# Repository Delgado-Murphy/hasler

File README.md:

# Hasler Music Box

<sub><i>A Delgado &amp; Murphy restoration</i></sub>

A Swiss radio from the 1960s that plays music again.

**Have a Hasler at home? → [Using your Hasler](docs/using.md)**

The **Hasler HM** was built in Bern around 1964 for Telefónica's *Hilo Musical*,
a service that sent music to homes over the telephone line. Its piano keys chose
one of six music channels. Today the same keys play internet radio, Spotify and
YouTube Music, and the radio is a speaker for your phone. The keys, the knobs,
the pilot lamp and the original speaker all still work.

## What it can do

- **Press a key, hear music.** No phone, no app.
- **Nearly 600 radio stations** from about 120 countries, each one played on
  a Hasler before it went in.
- **A speaker for your phone:** Spotify, AirPlay, Bluetooth and other music
  apps. Guests on your Wi-Fi can play too.
- **Several rooms.** Two or more Haslers play the same music in step.
- **Two knobs, like the old radio.** Volume, with a ceiling that protects the
  old speaker, and tone, which also switches the radio off.
- **A pilot lamp that talks:** amber for the radio, blue for a phone, a dim
  ember when asleep, dark when it is safe to unplug.
- **A key page** in your browser to choose the music on each key.
- **Safe updates** that install by themselves at night, and step back if
  something doesn't work.
- **Home Assistant**, if you want it. Everything works without it.

**Living with a Hasler?** [Using your Hasler](docs/using.md) starts with the
first ten minutes. The [pilot lamp](docs/lamp.md) has every colour, and
[Remote help](docs/remote-help.md) explains how the makers can look at your
radio from afar, only when you say so.

What changed in each version: the
[releases page](https://delgado-murphy.github.io/hasler-releases/).

---

## For makers and contributors

<!-- docs/img/hasler.jpg is a render of the HAT board for now; swap in a photo of the finished cabinet when there is one. -->

Inside: a Raspberry Pi, a modern amplifier and our own board (the Hasler
HAT), wired to the cabinet's original keys, knobs, lamp and speaker.

| You are... | Read this |
|---|---|
| **Building one** | [Build guide](docs/build-guide.md), then [Hardware](docs/hardware.md) |
| **Helping with the code** | [How it works](docs/architecture.md), then [Contributing](docs/contributing.md) |
| **Curious what changed** | [Releases](https://delgado-murphy.github.io/hasler-releases/) and the [changelog](CHANGELOG.md) |

**For makers**

- [Build guide](docs/build-guide.md): from an empty cabinet to a working radio, step by step.
- [A new SD card](docs/new-install.md): the radio's software from a blank card, headless, from a signed release.
- [Hardware](docs/hardware.md): parts list, wiring, power and protection.
- [The knobs' sound effects](docs/sound.md): the tone knob's effects and how a cabinet's knobs get them.
- [Multiroom and casting](docs/multiroom.md): how Haslers play in step (Snapcast), room names, AirPlay, UPnP, Bluetooth, Spotify.
- [The pilot lamp](docs/lamp.md): the light language, and the design the code follows.
- [Remote help](docs/remote-help.md): the makers' side, the tailnet and approving a radio.
- [Hasler HM panel survey](docs/variants/hasler-hm.md): measuring this cabinet's keys, knobs and speaker.
- [Prototype board](docs/prototype/README.md), and the Hasler HAT: [brief](docs/hat/BRIEF.md), [design](docs/hat/DESIGN.md), [ordering and bring-up](hardware/hat/ORDERING.md).

**For contributors and maintainers**

- [How the radio works](docs/architecture.md): the moving parts on one page, with diagrams.
- [Contributing](docs/contributing.md): where things are, running it on a laptop, the tests, how a cabinet's panel is described.
- [Security](SECURITY.md): how to report a security problem (privately, not in an issue).
- [Over-the-air updates](docs/ota.md): how updates stay safe.
- [Releasing](docs/release.md): how a new version is built, signed and published.
- [OTA formats](docs/ota-format.md): the exact file formats (a contract between the builder and the radio).

### How it works, in one picture

```
keys ───▶ MCP23017 (or Pi GPIO) ──┐
knobs ──▶ ADS1115 ────────────────┤
                                  ▼
                               haslerd ──▶ pilot lamp
                    ┌─────────────┼──────────────┬───────────────────┐
                    ▼             ▼              ▼                   ▼
             MPD (moOde)    go-librespot     key page :80/:8080   Home Assistant
          radio, YouTube      Spotify                            (optional)
              Music

MPD │ go-librespot │ Bluetooth │ AirPlay │ UPnP ──▶ Amp4 Pro (hardware mixer = the knob) ──▶ original speaker
                         │
                         └─ in a group: Snapcast ──▶ the other Haslers (each through its own amp and knob)
```

More detail, with diagrams: [How the radio works](docs/architecture.md).

`haslerd` is our small service on the Pi. It reads the keys and knobs, starts
the music, drives the lamp and serves the key page. The music system underneath
is [moOde audio](https://moodeaudio.org/). Bluetooth, AirPlay (shairport-sync)
and UPnP come from moOde; Spotify comes from go-librespot; YouTube Music
streams are found by yt-dlp; the tone knob's effects run in CamillaDSP
([sound.md](docs/sound.md)). Several Haslers play in step through
[Snapcast](https://github.com/badaix/snapcast) ([multiroom.md](docs/multiroom.md)).

**More cabinets are coming.** An *Excelsior* and others are waiting, and their
panels work differently (for example, keys that lock down). So the panel is
**data, not code**: one service, a few control types, and one YAML file per
cabinet in `config/variants/`.

### Licence

Hasler's code is [MIT](LICENSE). Two exceptions: the moOde patch in
`config/moode/` is GPL-3.0-or-later, because it changes moOde
([config/moode/LICENSE](config/moode/LICENSE)), and the HAT hardware design
(`hardware/hat/` and its notes in `docs/hat/`) is
[CERN-OHL-P-2.0](hardware/hat/LICENSE). Releases also bundle
go-librespot (GPL-3.0), Deno (MIT), two fonts (SIL OFL 1.1) and Python
packages under their own licences; [THIRD_PARTY_NOTICES.md](THIRD_PARTY_NOTICES.md)
lists them, and every release carries it with the full texts in `licenses/`.

---

<sub>Delgado &amp; Murphy · Hasler HM, Bern 1964 — restored 2026</sub>

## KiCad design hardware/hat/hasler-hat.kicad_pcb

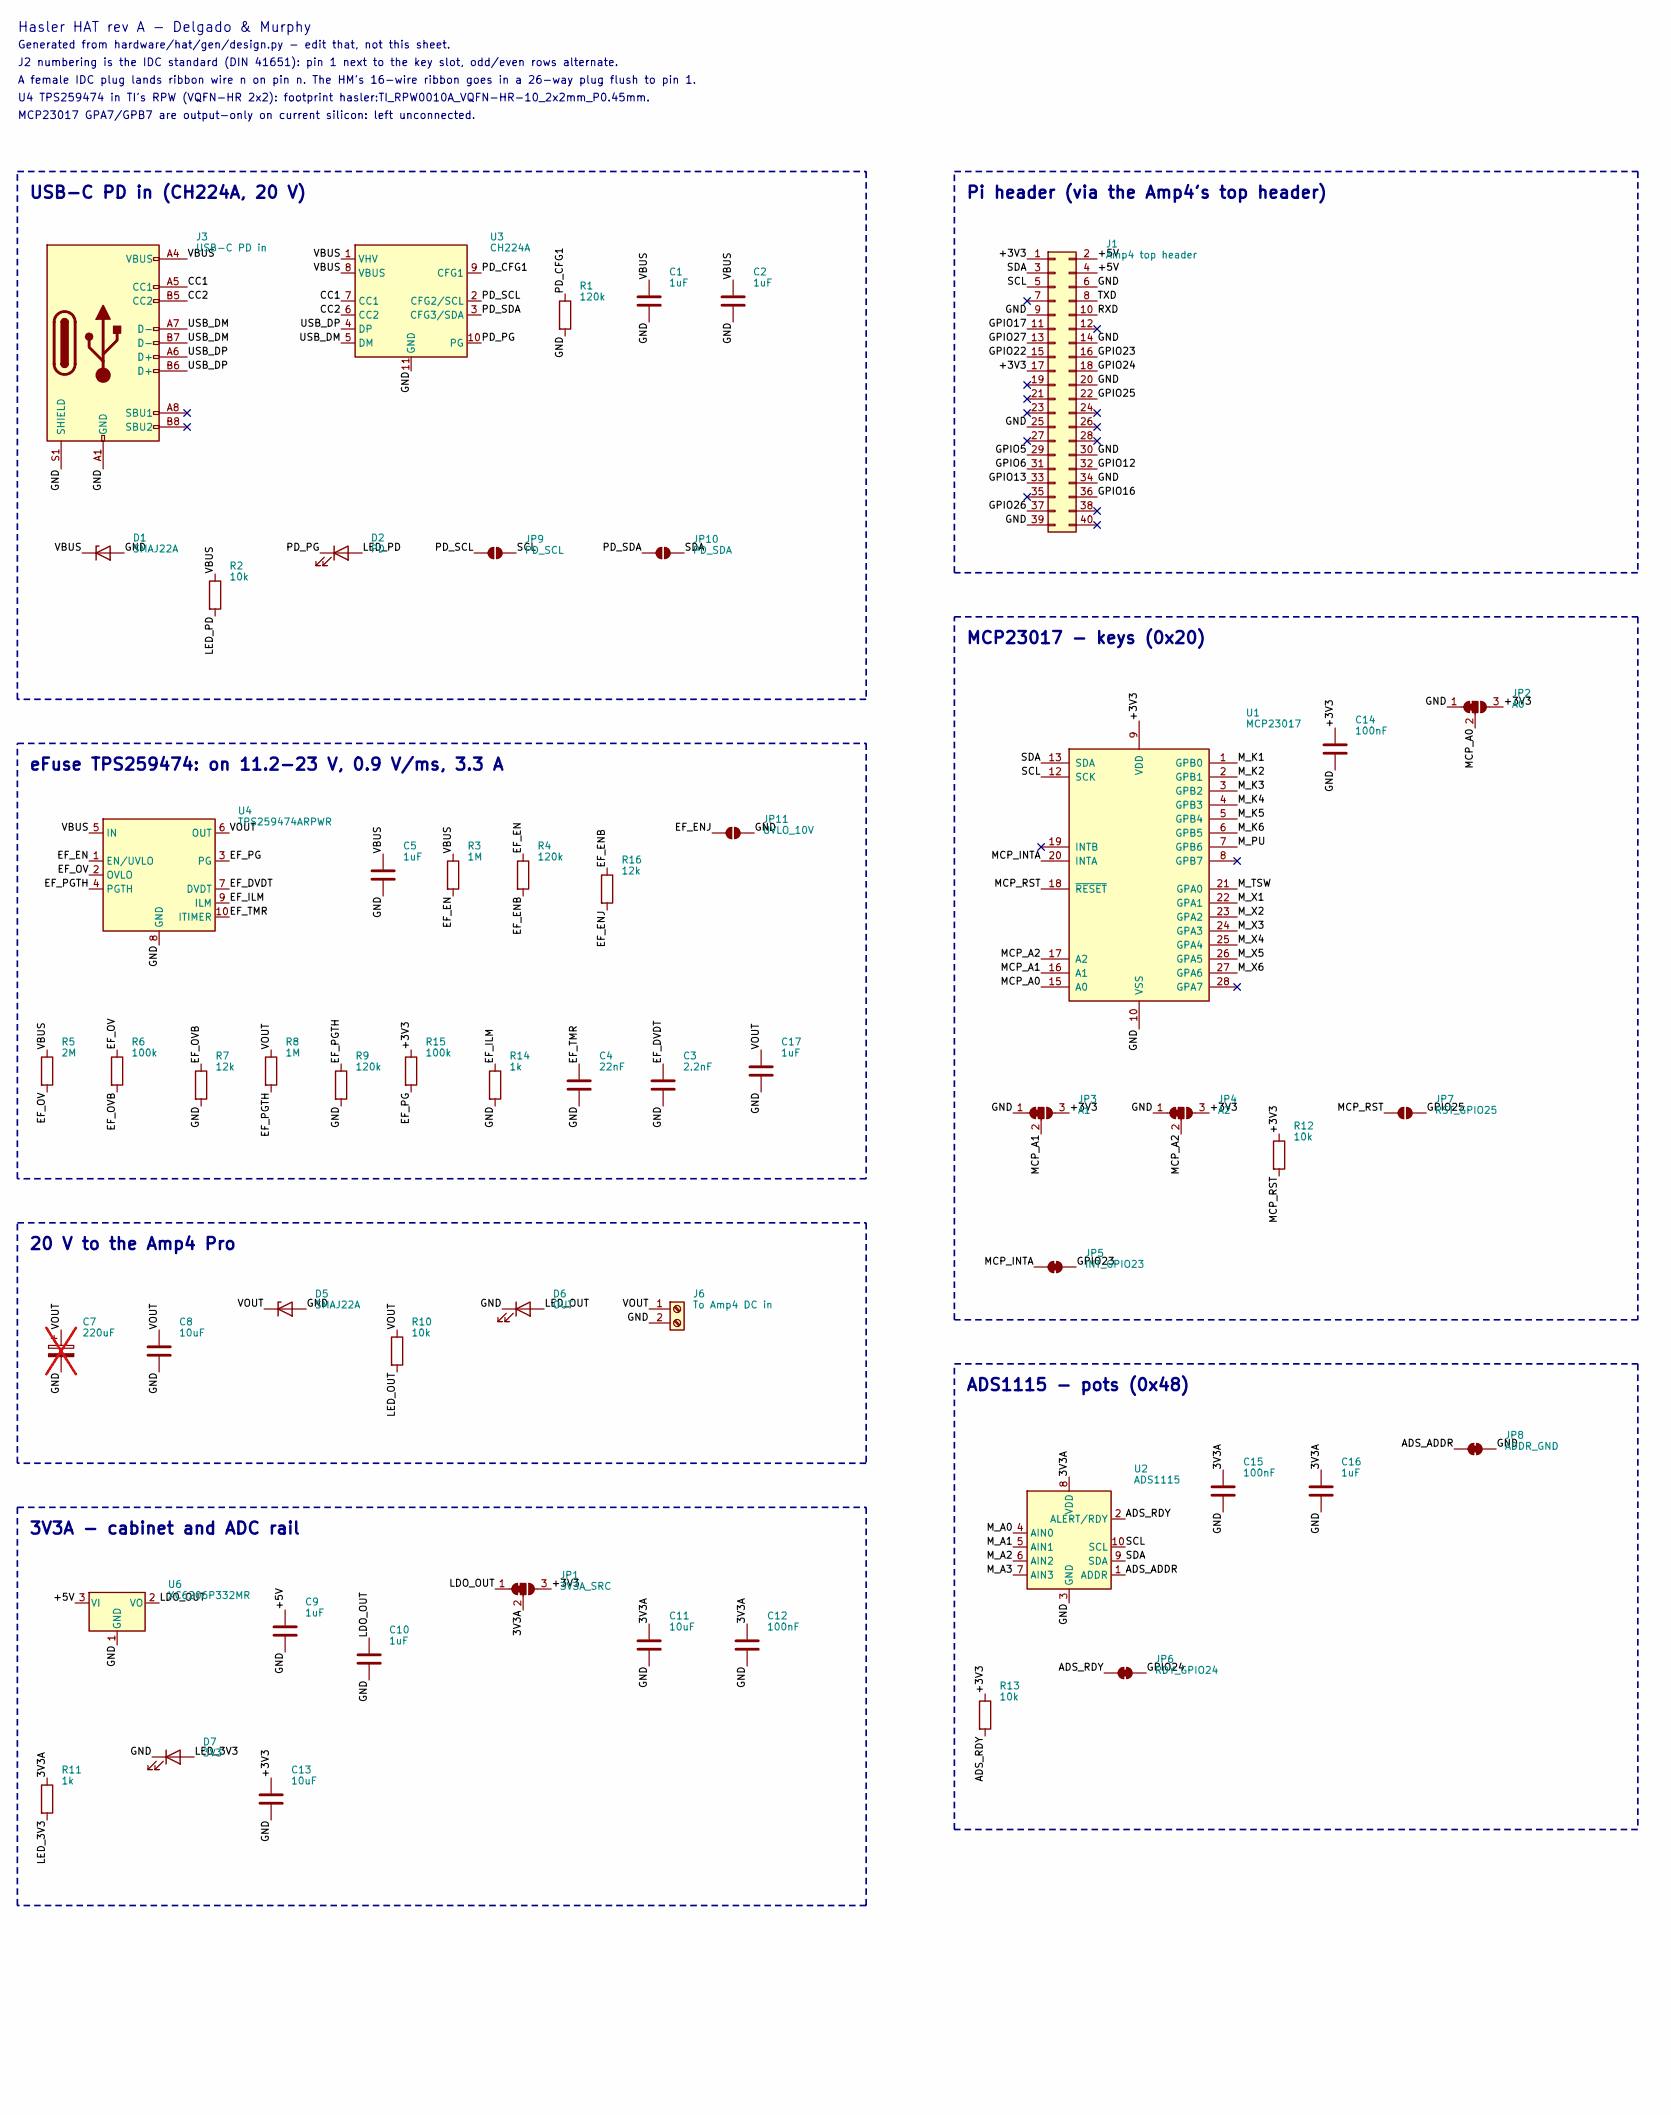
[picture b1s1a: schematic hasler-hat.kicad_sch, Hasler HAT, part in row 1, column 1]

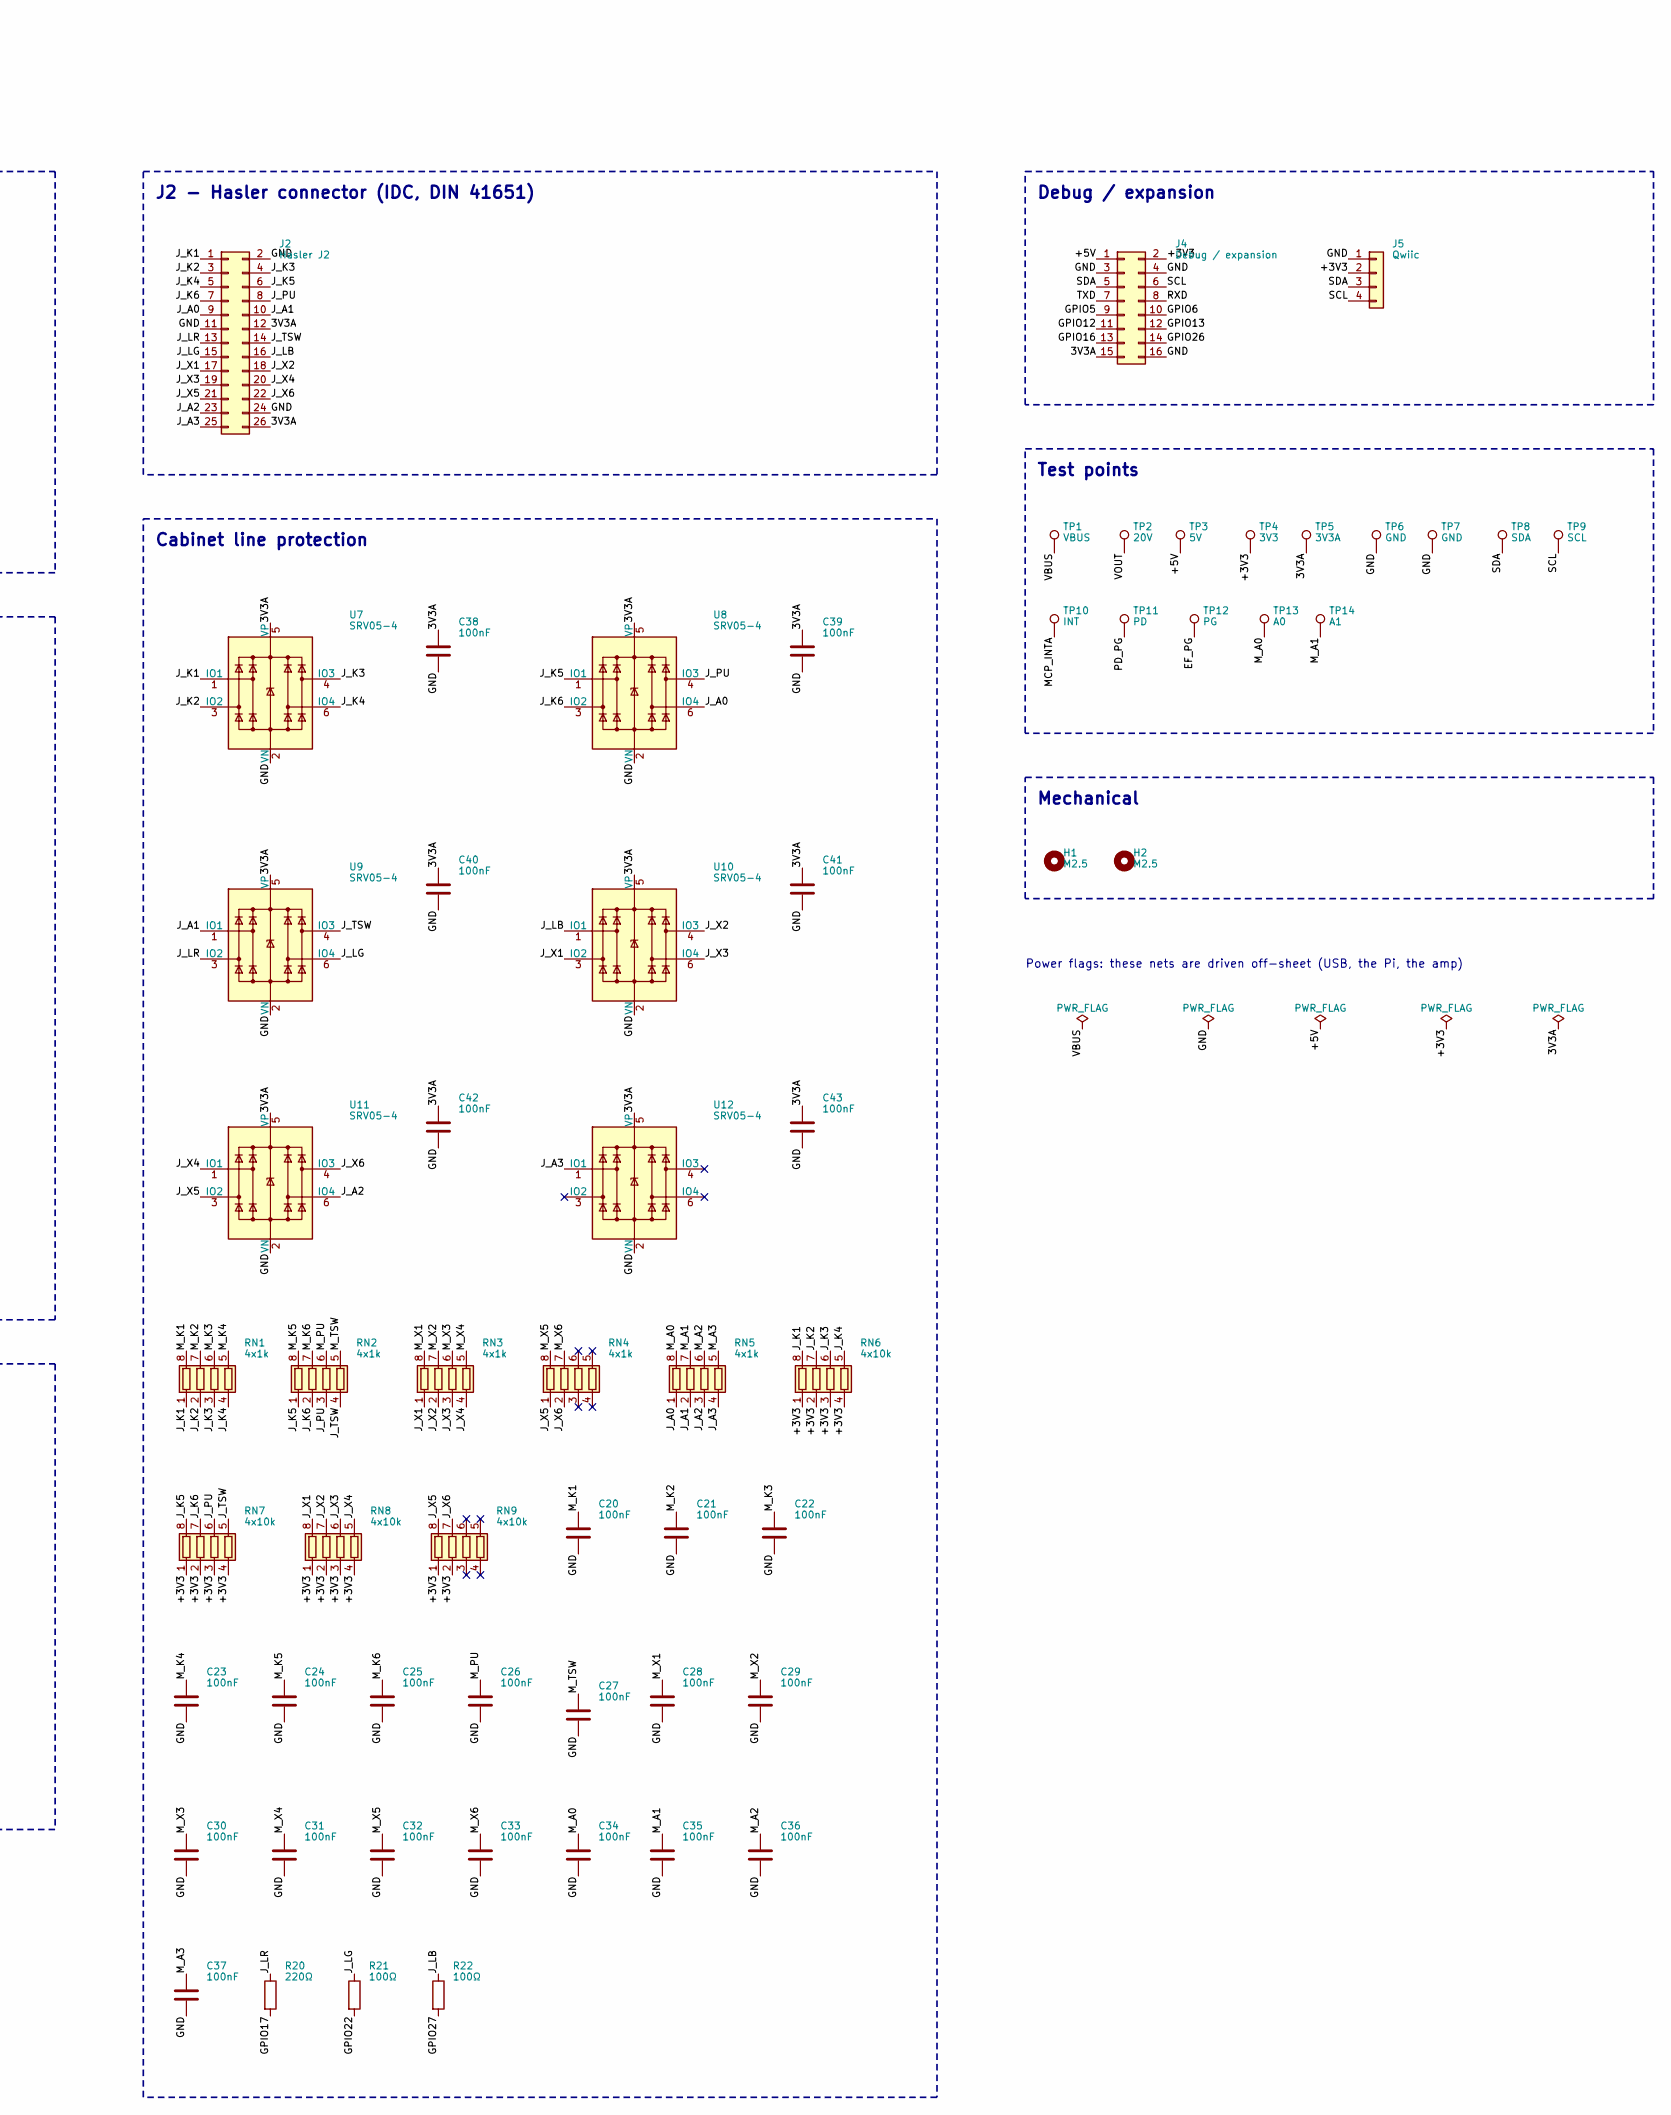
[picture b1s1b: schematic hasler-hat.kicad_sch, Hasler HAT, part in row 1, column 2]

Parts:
C1: 1uF; C_0805_2012Metric; MPN 1uF; LCSC C28323
C2, C5, C9, C10, C16, C17: 1uF; C_0603_1608Metric; MPN 1uF; LCSC C15849
C3: 2.2nF; C_0603_1608Metric; MPN 2.2nF; LCSC C1604
C4: 22nF; C_0402_1005Metric; MPN 22nF; LCSC C1532
C7: 220uF; CP_Elec_8x10; MPN 220uF; LCSC C970697; not fitted
C8: 10uF; C_1206_3216Metric; MPN 10uF; LCSC C13585
C11, C13: 10uF; C_0805_2012Metric; MPN 10uF; LCSC C15850
C12, C14, C15, C20, C21, C22, C23, C24, C25, C26, C27, C28, C29, C30, C31, C32, C33, C34, C35, C36, C37, C38, C39, C40, C41, C42, C43: 100nF; C_0402_1005Metric; MPN 100nF; LCSC C1525
D1, D5: SMAJ22A; D_SMA; MPN SMAJ22A; LCSC C283896
D2: PD; LED_0603_1608Metric; MPN KT-0603Y; LCSC C2287
D6: OUT; LED_0603_1608Metric; MPN XL-1608UGC-04; LCSC C965804
D7: 3V3; LED_0603_1608Metric; MPN KT-0603R; LCSC C2286
H1, H2: M2.5; MountingHole_2.7mm_M2.5; MPN M2.5
J1: Amp4 top header; PinSocket_2x20_P2.54mm_Vertical; MPN 2.54-2*20P female 8.5 mm; LCSC C5124634
J2: Hasler J2; IDC-Header_2x13_P2.54mm_Vertical; MPN DC3-2.54-26PAS; LCSC C5156668
J3: USB-C PD in; USB_C_Receptacle_HRO_TYPE-C-31-M-12; MPN TYPE-C-31-M-12; LCSC C165948
J4: Debug / expansion; PinHeader_2x08_P2.54mm_Vertical; MPN PZ254-2-08-Z-8.5; LCSC C2894969
J5: Qwiic; JST_SH_SM04B-SRSS-TB_1x04-1MP_P1.00mm_Horizontal; MPN SM04B-SRSS-TB; LCSC C160404
J6: To Amp4 DC in; TerminalBlock_Kefa_KF350-3.5-2P_1x02_P3.50mm_Horizontal; MPN KF350-3.5-2P; LCSC C474892
JP1: 3V3A_SRC; SolderJumper-3_P1.3mm_Bridged12_RoundedPad1.0x1.5mm; MPN 3V3A_SRC
JP2: A0; SolderJumper-3_P1.3mm_Bridged12_RoundedPad1.0x1.5mm; MPN A0
JP3: A1; SolderJumper-3_P1.3mm_Bridged12_RoundedPad1.0x1.5mm; MPN A1
JP4: A2; SolderJumper-3_P1.3mm_Bridged12_RoundedPad1.0x1.5mm; MPN A2
JP5: INT_GPIO23; SolderJumper-2_P1.3mm_Bridged_RoundedPad1.0x1.5mm; MPN INT_GPIO23
JP6: RDY_GPIO24; SolderJumper-2_P1.3mm_Bridged_RoundedPad1.0x1.5mm; MPN RDY_GPIO24
JP7: RST_GPIO25; SolderJumper-2_P1.3mm_Open_RoundedPad1.0x1.5mm; MPN RST_GPIO25
JP8: ADDR_GND; SolderJumper-2_P1.3mm_Bridged_RoundedPad1.0x1.5mm; MPN ADDR_GND
JP9: PD_SCL; SolderJumper-2_P1.3mm_Open_RoundedPad1.0x1.5mm; MPN PD_SCL
JP10: PD_SDA; SolderJumper-2_P1.3mm_Open_RoundedPad1.0x1.5mm; MPN PD_SDA
JP11: UVLO_10V; SolderJumper-2_P1.3mm_Open_RoundedPad1.0x1.5mm; MPN UVLO_10V
R1, R4, R9: 120k; R_0603_1608Metric; MPN 120k; LCSC C25808
R2, R10, R12, R13: 10k; R_0603_1608Metric; MPN 10k; LCSC C25804
R3, R8: 1M; R_0603_1608Metric; MPN 1M; LCSC C22935
R5: 2M; R_0603_1608Metric; MPN 2M; LCSC C22976
R6, R15: 100k; R_0603_1608Metric; MPN 100k; LCSC C25803
R7, R16: 12k; R_0603_1608Metric; MPN 12k; LCSC C22790
R11: 1k; R_0603_1608Metric; MPN 1k; LCSC C21190
R14: 1k; R_0402_1005Metric; MPN 1k; LCSC C11702
R20: 220Ω; R_0603_1608Metric; MPN 220Ω; LCSC C22962
R21, R22: 100Ω; R_0603_1608Metric; MPN 100Ω; LCSC C22775
RN1, RN2, RN3, RN4, RN5: 4x1k; R_Array_Convex_4x0603; MPN 4D03WGJ0102T5E; LCSC C20197
RN6, RN7, RN8, RN9: 4x10k; R_Array_Convex_4x0603; MPN 4D03WGJ0103T5E; LCSC C29718
TP1: VBUS; TestPoint_Pad_D1.0mm; MPN VBUS
TP2: 20V; TestPoint_Pad_D1.0mm; MPN 20V
TP3: 5V; TestPoint_Pad_D1.0mm; MPN 5V
TP4: 3V3; TestPoint_Pad_D1.0mm; MPN 3V3
TP5: 3V3A; TestPoint_Pad_D1.0mm; MPN 3V3A
TP6, TP7: GND; TestPoint_Pad_D1.0mm; MPN GND
TP8: SDA; TestPoint_Pad_D1.0mm; MPN SDA
TP9: SCL; TestPoint_Pad_D1.0mm; MPN SCL
TP10: INT; TestPoint_Pad_D1.0mm; MPN INT
TP11: PD; TestPoint_Pad_D1.0mm; MPN PD
TP12: PG; TestPoint_Pad_D1.0mm; MPN PG
TP13: A0; TestPoint_Pad_D1.0mm; MPN A0
TP14: A1; TestPoint_Pad_D1.0mm; MPN A1
U1: MCP23017; SSOP-28_5.3x10.2mm_P0.65mm; MPN MCP23017-E/SS; LCSC C506653
U2: ADS1115; VSSOP-10_3x3mm_P0.5mm; MPN ADS1115IDGSR; LCSC C37593
U3: CH224A; SSOP-10-1EP_3.9x4.9mm_P1mm_EP2.1x3.3mm; MPN CH224A; LCSC C42459160
U4: TPS259474ARPWR; TI_RPW0010A_VQFN-HR-10_2x2mm_P0.45mm; MPN TPS259474ARPWR; LCSC C3662807
U6: XC6206P332MR; SOT-23-3; MPN XC6206P332MR-G; LCSC C5446
U7, U8, U9, U10, U11, U12: SRV05-4; SOT-23-6; MPN SRV05-4.TCT; LCSC C13612

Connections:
/3V3A: C11.1, C12.1, C15.1, C16.1, C38.1, C39.1, C40.1, C41.1, C42.1, C43.1, J2.12, J2.26, J4.15, JP1.2 (C), R11.1, TP5.1, U2.8 (VDD), U7.5 (VP), U8.5 (VP), U9.5 (VP), U10.5 (VP), U11.5 (VP), U12.5 (VP)
/+3V3: C13.1, C14.1, J1.1, J1.17, J4.2, J5.2, JP1.3 (B), JP2.3 (B), JP3.3 (B), JP4.3 (B), R12.1, R13.1, R15.1, RN6.1 (R1.1), RN6.2 (R2.1), RN6.3 (R3.1), RN6.4 (R4.1), RN7.1 (R1.1), RN7.2 (R2.1), RN7.3 (R3.1), RN7.4 (R4.1), RN8.1 (R1.1), RN8.2 (R2.1), RN8.3 (R3.1), RN8.4 (R4.1), RN9.1 (R1.1), RN9.2 (R2.1), TP4.1, U1.9 (VDD)
/+5V: C9.1, J1.2, J1.4, J4.1, TP3.1, U6.3 (VI)
/ADS_ADDR: JP8.1 (A), U2.1 (ADDR)
/ADS_RDY: JP6.1 (A), R13.2, U2.2 (ALERT/RDY)
/CC1: J3.A5 (CC1), U3.7 (CC1)
/CC2: J3.B5 (CC2), U3.6 (CC2)
/EF_DVDT: C3.1, U4.7 (DVDT)
/EF_EN: R3.2, R4.1, U4.1 (EN/UVLO)
/EF_ENB: R4.2, R16.1
/EF_ENJ: JP11.1 (A), R16.2
/EF_ILM: R14.1, U4.9 (ILM)
/EF_OV: R5.2, R6.1, U4.2 (OVLO)
/EF_OVB: R6.2, R7.1
/EF_PG: R15.2, TP12.1, U4.3 (PG)
/EF_PGTH: R8.2, R9.1, U4.4 (PGTH)
/EF_TMR: C4.1, U4.10 (ITIMER)
/GND: C1.2, C2.2, C3.2, C4.2, C5.2, C7.2, C8.2, C9.2, C10.2, C11.2, C12.2, C13.2, C14.2, C15.2, C16.2, C17.2, C20.2, C21.2, C22.2, C23.2, C24.2, C25.2, C26.2, C27.2, C28.2, C29.2, C30.2, C31.2, C32.2, C33.2, C34.2, C35.2, C36.2, C37.2, C38.2, C39.2, C40.2, C41.2, C42.2, C43.2, D1.2 (A), D5.2 (A), D6.1 (K), D7.1 (K), J1.6, J1.9, J1.14, J1.20, J1.25, J1.30, J1.34, J1.39, J2.2, J2.11, J2.24, J3.A1 (GND), J3.A12 (GND), J3.B1 (GND), J3.B12 (GND), J3.S1 (SHIELD), J4.3, J4.4, J4.16, J5.1, J6.2, JP2.1 (A), JP3.1 (A), JP4.1 (A), JP8.2 (B), JP11.2 (B), R1.2, R7.2, R9.2, R14.2, TP6.1, TP7.1, U1.10 (VSS), U2.3 (GND), U3.11 (GND), U4.8 (GND), U6.1 (GND), U7.2 (VN), U8.2 (VN), U9.2 (VN), U10.2 (VN), U11.2 (VN), U12.2 (VN)
/GPIO5: J1.29, J4.9
/GPIO6: J1.31, J4.10
/GPIO12: J1.32, J4.11
/GPIO13: J1.33, J4.12
/GPIO16: J1.36, J4.13
/GPIO17: J1.11, R20.2
/GPIO22: J1.15, R21.2
/GPIO23: J1.16, JP5.2 (B)
/GPIO24: J1.18, JP6.2 (B)
/GPIO25: J1.22, JP7.2 (B)
/GPIO26: J1.37, J4.14
/GPIO27: J1.13, R22.2
/J_A0: J2.9, RN5.1 (R1.1), U8.6 (IO4)
/J_A1: J2.10, RN5.2 (R2.1), U9.1 (IO1)
/J_A2: J2.23, RN5.3 (R3.1), U11.6 (IO4)
/J_A3: J2.25, RN5.4 (R4.1), U12.1 (IO1)
/J_K1: J2.1, RN1.1 (R1.1), RN6.8 (R1.2), U7.1 (IO1)
/J_K2: J2.3, RN1.2 (R2.1), RN6.7 (R2.2), U7.3 (IO2)
/J_K3: J2.4, RN1.3 (R3.1), RN6.6 (R3.2), U7.4 (IO3)
/J_K4: J2.5, RN1.4 (R4.1), RN6.5 (R4.2), U7.6 (IO4)
/J_K5: J2.6, RN2.1 (R1.1), RN7.8 (R1.2), U8.1 (IO1)
/J_K6: J2.7, RN2.2 (R2.1), RN7.7 (R2.2), U8.3 (IO2)
/J_LB: J2.16, R22.1, U10.1 (IO1)
/J_LG: J2.15, R21.1, U9.6 (IO4)
/J_LR: J2.13, R20.1, U9.3 (IO2)
/J_PU: J2.8, RN2.3 (R3.1), RN7.6 (R3.2), U8.4 (IO3)
/J_TSW: J2.14, RN2.4 (R4.1), RN7.5 (R4.2), U9.4 (IO3)
/J_X1: J2.17, RN3.1 (R1.1), RN8.8 (R1.2), U10.3 (IO2)
/J_X2: J2.18, RN3.2 (R2.1), RN8.7 (R2.2), U10.4 (IO3)
/J_X3: J2.19, RN3.3 (R3.1), RN8.6 (R3.2), U10.6 (IO4)
/J_X4: J2.20, RN3.4 (R4.1), RN8.5 (R4.2), U11.1 (IO1)
/J_X5: J2.21, RN4.1 (R1.1), RN9.8 (R1.2), U11.3 (IO2)
/J_X6: J2.22, RN4.2 (R2.1), RN9.7 (R2.2), U11.4 (IO3)
/LDO_OUT: C10.1, JP1.1 (A), U6.2 (VO)
/LED_3V3: D7.2 (A), R11.2
/LED_OUT: D6.2 (A), R10.2
/LED_PD: D2.2 (A), R2.2
/MCP_A0: JP2.2 (C), U1.15 (A0)
/MCP_A1: JP3.2 (C), U1.16 (A1)
/MCP_A2: JP4.2 (C), U1.17 (A2)
/MCP_INTA: JP5.1 (A), TP10.1, U1.20 (INTA)
/MCP_RST: JP7.1 (A), R12.2, U1.18 (~RESET)
/M_A0: C34.1, RN5.8 (R1.2), TP13.1, U2.4 (AIN0)
/M_A1: C35.1, RN5.7 (R2.2), TP14.1, U2.5 (AIN1)
/M_A2: C36.1, RN5.6 (R3.2), U2.6 (AIN2)
/M_A3: C37.1, RN5.5 (R4.2), U2.7 (AIN3)
/M_K1: C20.1, RN1.8 (R1.2), U1.1 (GPB0)
/M_K2: C21.1, RN1.7 (R2.2), U1.2 (GPB1)
/M_K3: C22.1, RN1.6 (R3.2), U1.3 (GPB2)
/M_K4: C23.1, RN1.5 (R4.2), U1.4 (GPB3)
/M_K5: C24.1, RN2.8 (R1.2), U1.5 (GPB4)
/M_K6: C25.1, RN2.7 (R2.2), U1.6 (GPB5)
/M_PU: C26.1, RN2.6 (R3.2), U1.7 (GPB6)
/M_TSW: C27.1, RN2.5 (R4.2), U1.21 (GPA0)
/M_X1: C28.1, RN3.8 (R1.2), U1.22 (GPA1)
/M_X2: C29.1, RN3.7 (R2.2), U1.23 (GPA2)
/M_X3: C30.1, RN3.6 (R3.2), U1.24 (GPA3)
/M_X4: C31.1, RN3.5 (R4.2), U1.25 (GPA4)
/M_X5: C32.1, RN4.8 (R1.2), U1.26 (GPA5)
/M_X6: C33.1, RN4.7 (R2.2), U1.27 (GPA6)
/PD_CFG1: R1.1, U3.9 (CFG1)
/PD_PG: D2.1 (K), TP11.1, U3.10 (PG)
/PD_SCL: JP9.1 (A), U3.2 (CFG2/SCL)
/PD_SDA: JP10.1 (A), U3.3 (CFG3/SDA)
/RXD: J1.10, J4.8
/SCL: J1.5, J4.6, J5.4, JP9.2 (B), TP9.1, U1.12 (SCK), U2.10 (SCL)
/SDA: J1.3, J4.5, J5.3, JP10.2 (B), TP8.1, U1.13 (SDA), U2.9 (SDA)
/TXD: J1.8, J4.7
/USB_DM: J3.A7 (D-), J3.B7 (D-), U3.5 (DM)
/USB_DP: J3.A6 (D+), J3.B6 (D+), U3.4 (DP)
/VBUS: C1.1, C2.1, C5.1, D1.1 (K), J3.A4 (VBUS), J3.A9 (VBUS), J3.B4 (VBUS), J3.B9 (VBUS), R2.1, R3.1, R5.1, TP1.1, U3.1 (VHV), U3.8 (VBUS), U4.5 (IN)
/VOUT: C7.1, C8.1, C17.1, D5.1 (K), J6.1, R8.1, R10.1, TP2.1, U4.6 (OUT)

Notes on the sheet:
USB-C PD in (CH224A, 20 V)
eFuse TPS259474: on 11.2-23 V, 0.9 V/ms, 3.3 A
20 V to the Amp4 Pro
3V3A - cabinet and ADC rail
Pi header (via the Amp4's top header)
MCP23017 - keys (0x20)
ADS1115 - pots (0x48)
J2 - Hasler connector (IDC, DIN 41651)
Cabinet line protection
Debug / expansion
Test points
Mechanical
Power flags: these nets are driven off-sheet (USB, the Pi, the amp)
Hasler HAT rev A - Delgado & Murphy
Generated from hardware/hat/gen/design.py - edit that, not this sheet.
J2 numbering is the IDC standard (DIN 41651): pin 1 next to the key slot, odd/even rows alternate.
A female IDC plug lands ribbon wire n on pin n. The HM's 16-wire ribbon goes in a 26-way plug flush to pin 1.
U4 TPS259474 in TI's RPW (VQFN-HR 2x2): footprint hasler:TI_RPW0010A_VQFN-HR-10_2x2mm_P0.45mm.
MCP23017 GPA7/GPB7 are output-only on current silicon: left unconnected.

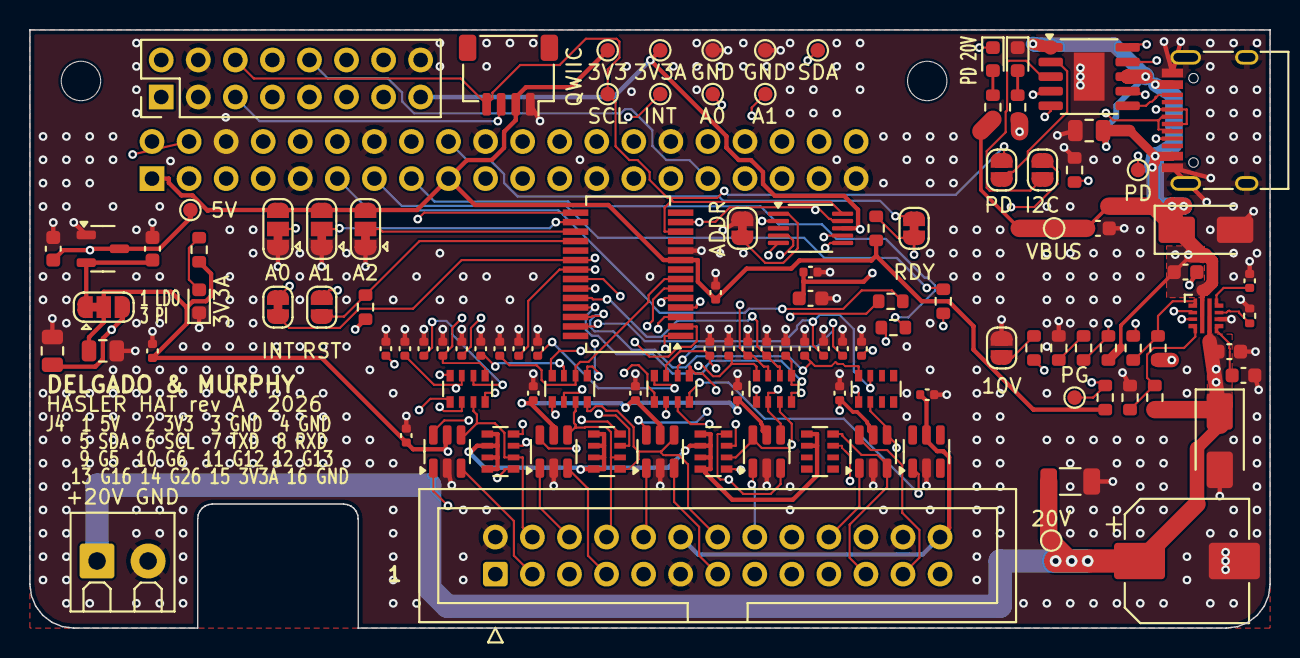
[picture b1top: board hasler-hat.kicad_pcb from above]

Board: 4 copper layers, 85.0 x 41.0 mm, 117 parts (1 on the bottom side), 90 nets.

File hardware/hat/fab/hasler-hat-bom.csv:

Comment,Designator,Footprint,LCSC Part #
1uF,C1,C_0805_2012Metric,C28323
10uF,"C11,C13",C_0805_2012Metric,C15850
100nF,"C12,C14,C15,C20,C21,C22,C23,C24,C25,C26,C27,C28,C29,C30,C31,C32,C33,C34,C35,C36,C37,C38,C39,C40,C41,C42,C43",C_0402_1005Metric,C1525
1uF,"C2,C5,C9,C10,C16,C17",C_0603_1608Metric,C15849
2.2nF,C3,C_0603_1608Metric,C1604
22nF,C4,C_0402_1005Metric,C1532
10uF,C8,C_1206_3216Metric,C13585
SMAJ22A,"D1,D5",D_SMA,C283896
KT-0603Y,D2,LED_0603_1608Metric,C2287
XL-1608UGC-04,D6,LED_0603_1608Metric,C965804
KT-0603R,D7,LED_0603_1608Metric,C2286
2.54-2*20P female 8.5 mm,J1,PinSocket_2x20_P2.54mm_Vertical,C5124634
DC3-2.54-26PAS,J2,IDC-Header_2x13_P2.54mm_Vertical,C5156668
TYPE-C-31-M-12,J3,USB_C_Receptacle_HRO_TYPE-C-31-M-12,C165948
PZ254-2-08-Z-8.5,J4,PinHeader_2x08_P2.54mm_Vertical,C2894969
SM04B-SRSS-TB,J5,JST_SH_SM04B-SRSS-TB_1x04-1MP_P1.00mm_Horizontal,C160404
KF350-3.5-2P,J6,TerminalBlock_Kefa_KF350-3.5-2P_1x02_P3.50mm_Horizontal,C474892
120k,"R1,R4,R9",R_0603_1608Metric,C25808
1k,R11,R_0603_1608Metric,C21190
1k,R14,R_0402_1005Metric,C11702
12k,"R7,R16",R_0603_1608Metric,C22790
10k,"R2,R10,R12,R13",R_0603_1608Metric,C25804
220Ω,R20,R_0603_1608Metric,C22962
100Ω,"R21,R22",R_0603_1608Metric,C22775
1M,"R3,R8",R_0603_1608Metric,C22935
2M,R5,R_0603_1608Metric,C22976
100k,"R6,R15",R_0603_1608Metric,C25803
4D03WGJ0102T5E,"RN1,RN2,RN3,RN4,RN5",R_Array_Convex_4x0603,C20197
4D03WGJ0103T5E,"RN6,RN7,RN8,RN9",R_Array_Convex_4x0603,C29718
MCP23017-E/SS,U1,SSOP-28_5.3x10.2mm_P0.65mm,C506653
ADS1115IDGSR,U2,VSSOP-10_3x3mm_P0.5mm,C37593
CH224A,U3,SSOP-10-1EP_3.9x4.9mm_P1mm_EP2.1x3.3mm,C42459160
TPS259474ARPWR,U4,TI_RPW0010A_VQFN-HR-10_2x2mm_P0.45mm,C3662807
XC6206P332MR-G,U6,SOT-23-3,C5446
SRV05-4.TCT,"U7,U8,U9,U10,U11,U12",SOT-23-6,C13612
